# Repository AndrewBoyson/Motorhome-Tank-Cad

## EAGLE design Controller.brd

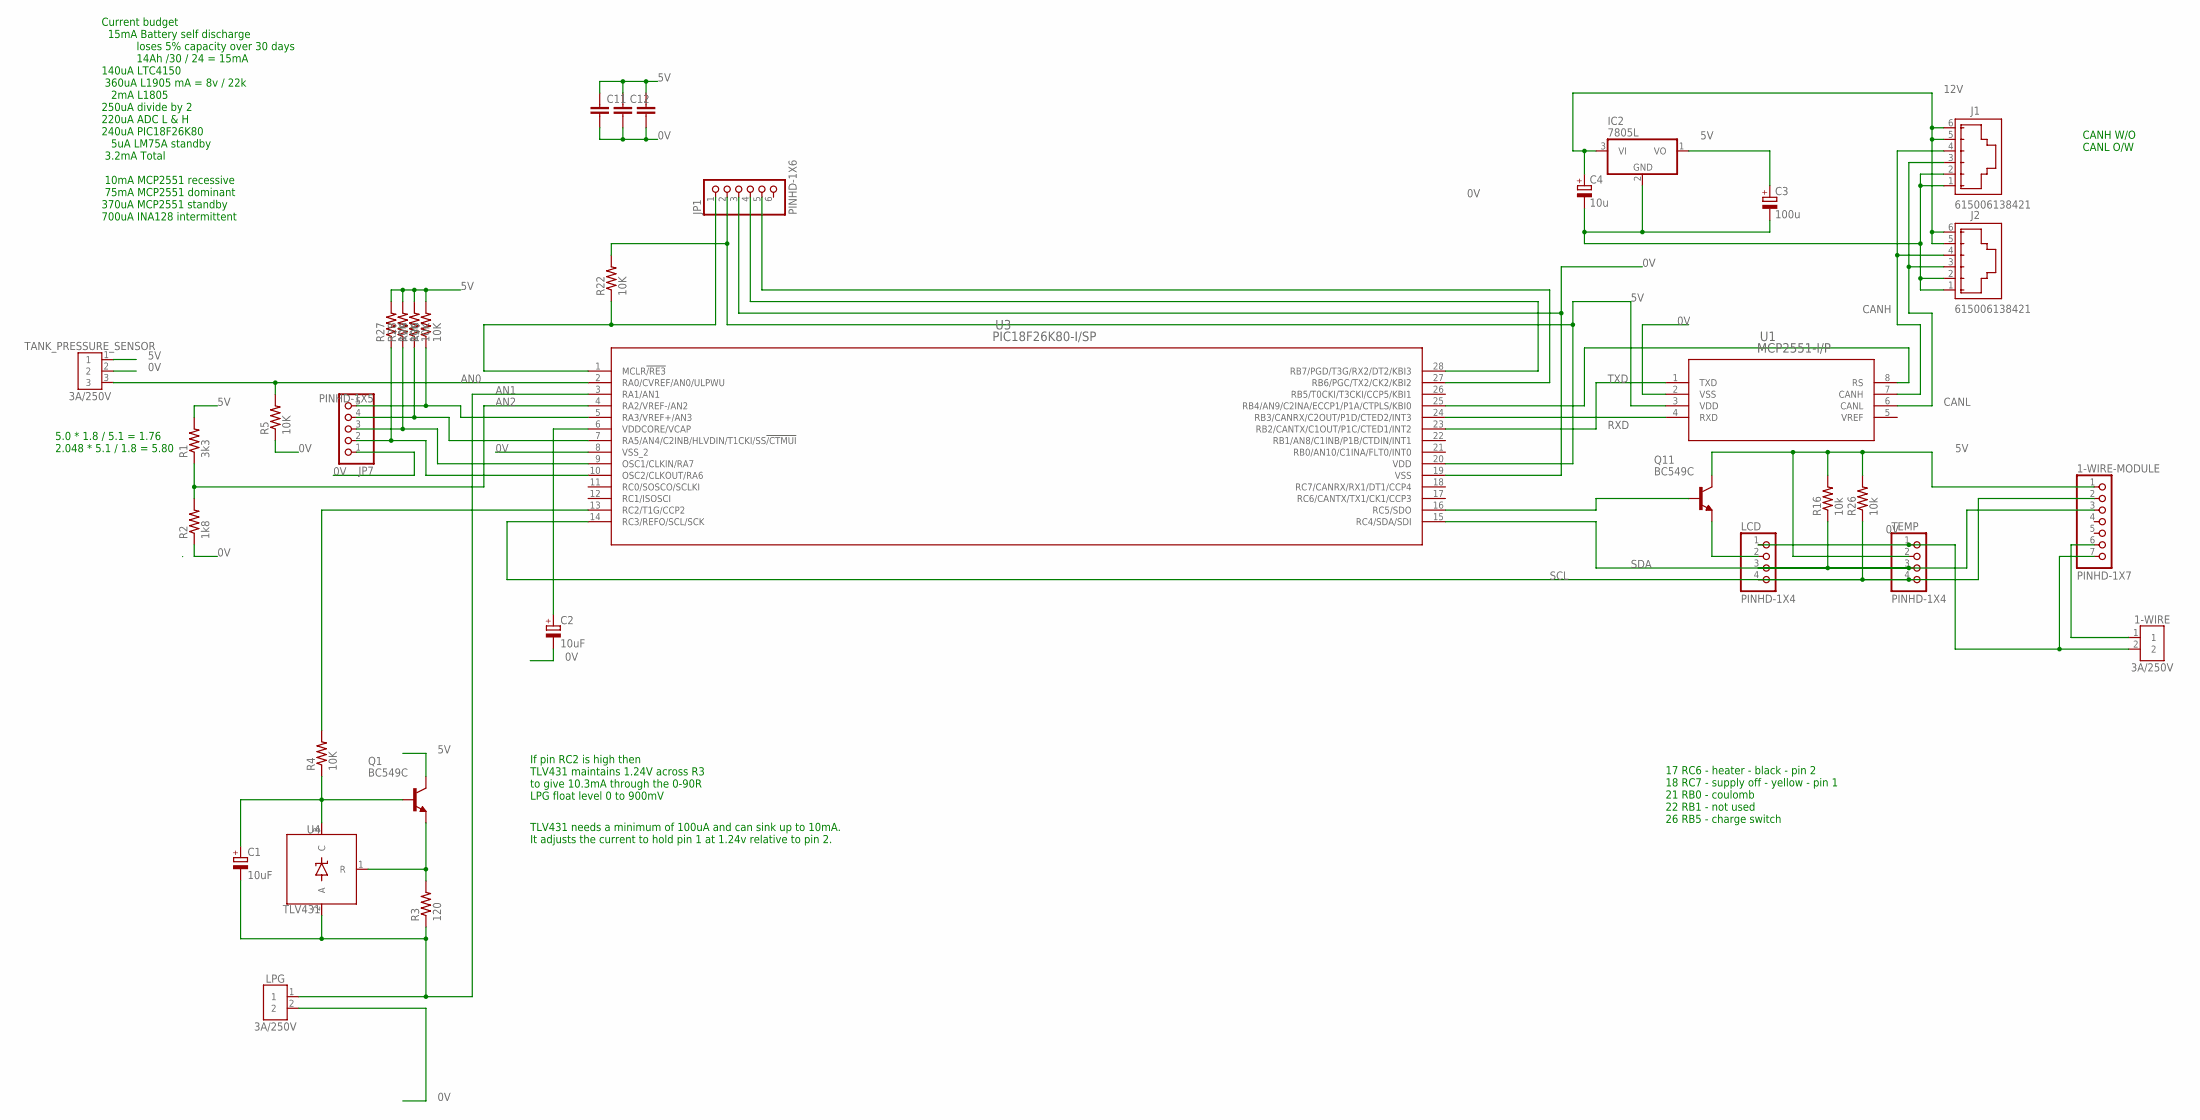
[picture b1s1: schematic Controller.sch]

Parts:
1-WIRE: 3A/250V; B2B-XH-A
1-WIRE-MODULE: PINHD-1X7; 1X07
C1, C2: 10uF; E3,5-8
C3: 100u; E3,5-8
C4: 10u; E3,5-8
C7, C11, C12: C2,5-3; C2.5-3
IC2: 7805L; TO92
J1, J2: 615006138421
JP1: PINHD-1X6; 1X06
JP7: PINHD-1X5; 1X05
LCD: PINHD-1X4; 1X04
LPG: 3A/250V; B2B-XH-A
Q1, Q11: BC549C; TO92-EBC
R1: 3k3; 0204/7
R2: 1k8; 0204/7
R3: 120; 0204/7
R4, R5, R22: 10K; 0204/7
R16, R26: 10k; 0204/7
R27, R28, R29, R30: 10K; 0204/7-90
TANK_PRESSURE_SENSOR: 3A/250V; B3B-XH-A
TEMP: PINHD-1X4; 1X04
U1: MCP2551-I/P; PDIP8_300MC_MCH
U3: PIC18F26K80-I/SP; SPDIP28_300MC_MCH
U4: TLV431; TO92

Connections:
0V: 1-WIRE.2, 1-WIRE-MODULE.7, C2.-, C3.-, C4.-, C7.2, C11.2, C12.2, IC2.2 (GND), J1.1, J1.2, J2.1, J2.2, JP1.3, JP7.1, LCD.1, LPG.2, R2.1, R5.1, TANK_PRESSURE_SENSOR.2, TEMP.1, U1.2 (VSS), U3.8 (VSS_2), U3.19 (VSS)
5V: 1-WIRE-MODULE.1, C3.+, C7.1, C11.1, C12.1, IC2.1 (VO), JP1.2, Q1.C, Q11.C, R1.2, R16.2, R22.2, R26.2, R27.2, R28.2, R29.2, R30.2, TANK_PRESSURE_SENSOR.1, TEMP.2, U1.3 (VDD), U3.20 (VDD)
12V: C4.+, IC2.3 (VI), J1.5, J1.6, J2.5, J2.6
AN0: R5.2, TANK_PRESSURE_SENSOR.3, U3.2 (RA0/CVREF/AN0/ULPWU)
AN1: C1.-, LPG.1, R3.1, U3.3 (RA1/AN1), U4.2 (A)
AN2: R1.1, R2.2, U3.4 (RA2/VREF-/AN2)
CANH: J1.4, J2.4, U1.7 (CANH)
CANL: J1.3, J2.3, U1.6 (CANL)
unnamed: JP1.1, R22.1, U3.1 (MCLR!/RE3)
unnamed: LCD.2, Q11.E
unnamed: JP1.4, U3.28 (RB7/PGD/T3G/RX2/DT2/KBI3)
unnamed: JP1.5, U3.27 (RB6/PGC/TX2/CK2/KBI2)
unnamed: R4.2, U3.13 (RC2/T1G/CCP2)
unnamed: 1-WIRE.1, 1-WIRE-MODULE.6
unnamed: Q1.E, R3.2, U4.1 (R)
unnamed: C2.+, U3.6 (VDDCORE/VCAP)
unnamed: C1.+, Q1.B, R4.1, U4.3 (C)
unnamed: Q11.B, U3.16 (RC5/SDO)
unnamed: JP7.5, R30.1, U3.5 (RA3/VREF+/AN3)
unnamed: JP7.4, R29.1, U3.7 (RA5/AN4/C2INB/HLVDIN/T1CKI/SS!/CTMUI)
unnamed: JP7.3, R28.1, U3.9 (OSC1/CLKIN/RA7)
unnamed: JP7.2, R27.1, U3.10 (OSC2/CLKOUT/RA6)
unnamed: U1.8 (RS), U3.25 (RB4/AN9/C2INA/ECCP1/P1A/CTPLS/KBI0)
RXD: U1.4 (RXD), U3.24 (RB3/CANRX/C2OUT/P1D/CTED2/INT3)
SCL: 1-WIRE-MODULE.2, LCD.4, R26.1, TEMP.4, U3.14 (RC3/REFO/SCL/SCK)
SDA: 1-WIRE-MODULE.3, LCD.3, R16.1, TEMP.3, U3.15 (RC4/SDA/SDI)
TXD: U1.1 (TXD), U3.23 (RB2/CANTX/C1OUT/P1C/CTED1/INT2)

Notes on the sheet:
TLV431 needs a minimum of 100uA and can sink up to 10mA. It adjusts the current to hold pin 1 at 1.24v relative to pin 2.
Current budget 15mA Battery self discharge loses 5% capacity over 30 days 14Ah /30 / 24 = 15mA 140uA LTC4150 360uA L1905 mA = 8v / 22k 2mA L1805 250uA divide by 2 220uA ADC L & H 240uA PIC18F26K80 5uA LM75A standby 3.2mA Total 10mA MCP2551 recessive 75mA MCP2551 dominant 370uA MCP2551 standby 700uA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
17 RC6 - heater - black - pin 2 18 RC7 - supply off - yellow - pin 1 21 RB0 - coulomb 22 RB1 - not used 26 RB5 - charge switch
If pin RC2 is high then TLV431 maintains 1.24V across R3 to give 10.3mA through the 0-90R LPG float level 0 to 900mV
CANH W/O CANL O/W
5.0 * 1.8 / 5.1 = 1.76 2.048 * 5.1 / 1.8 = 5.80

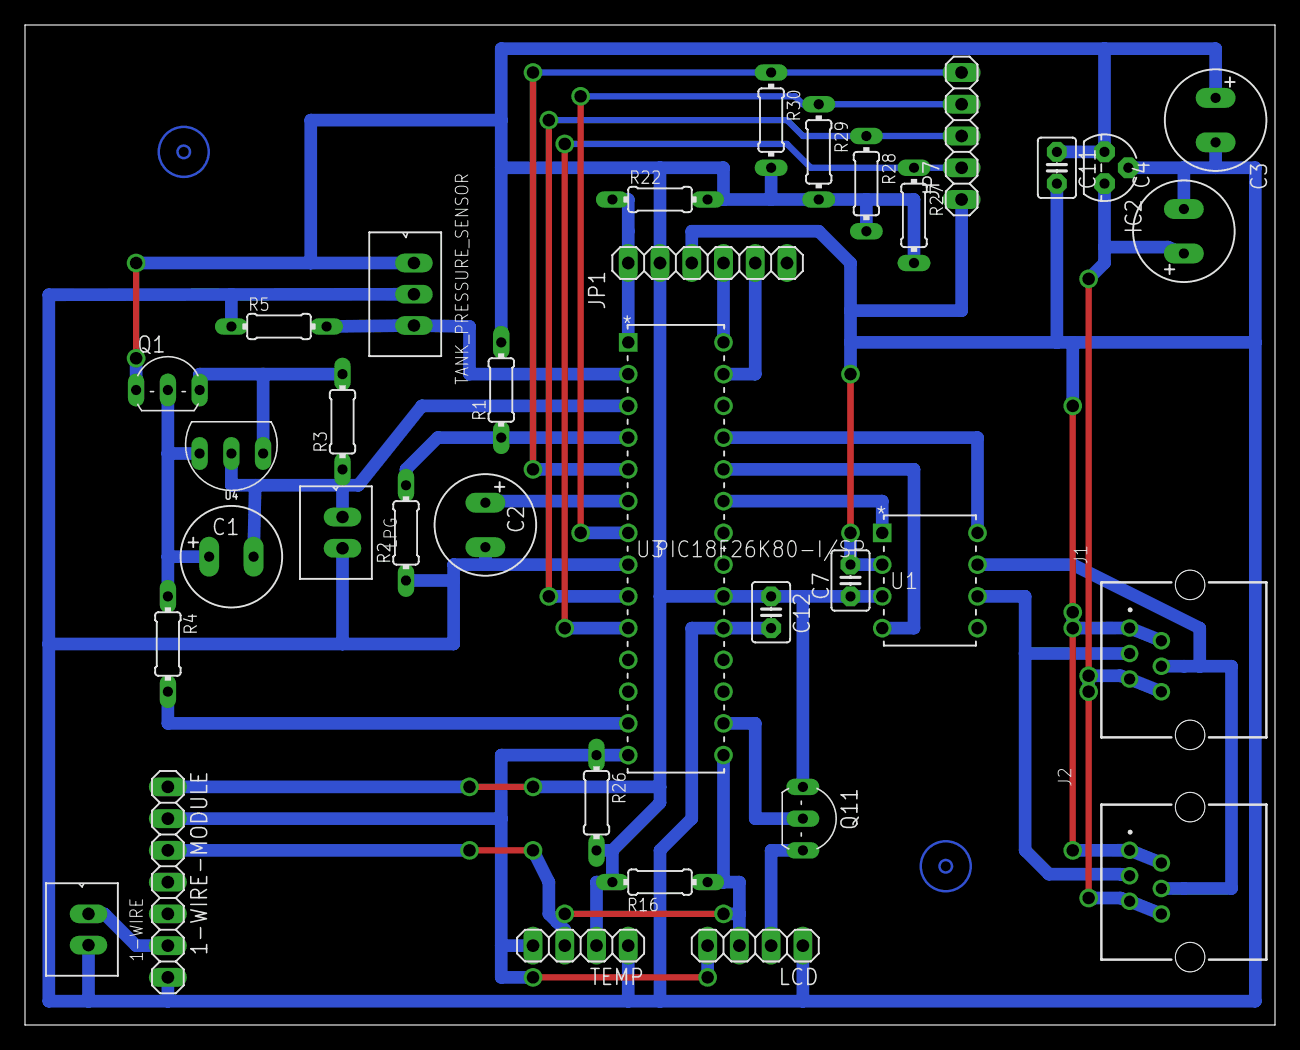
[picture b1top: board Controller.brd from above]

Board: 2 copper layers, 100.0 x 80.0 mm, 35 parts (0 on the bottom side), 27 nets.

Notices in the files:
parts and their libraries:
Wurth_Connectors_WR-MJ: Copyright: Würth Elektronik
COPYRIGHT: Copyright (C) 2021 Ultra Librarian. All rights reserved.
